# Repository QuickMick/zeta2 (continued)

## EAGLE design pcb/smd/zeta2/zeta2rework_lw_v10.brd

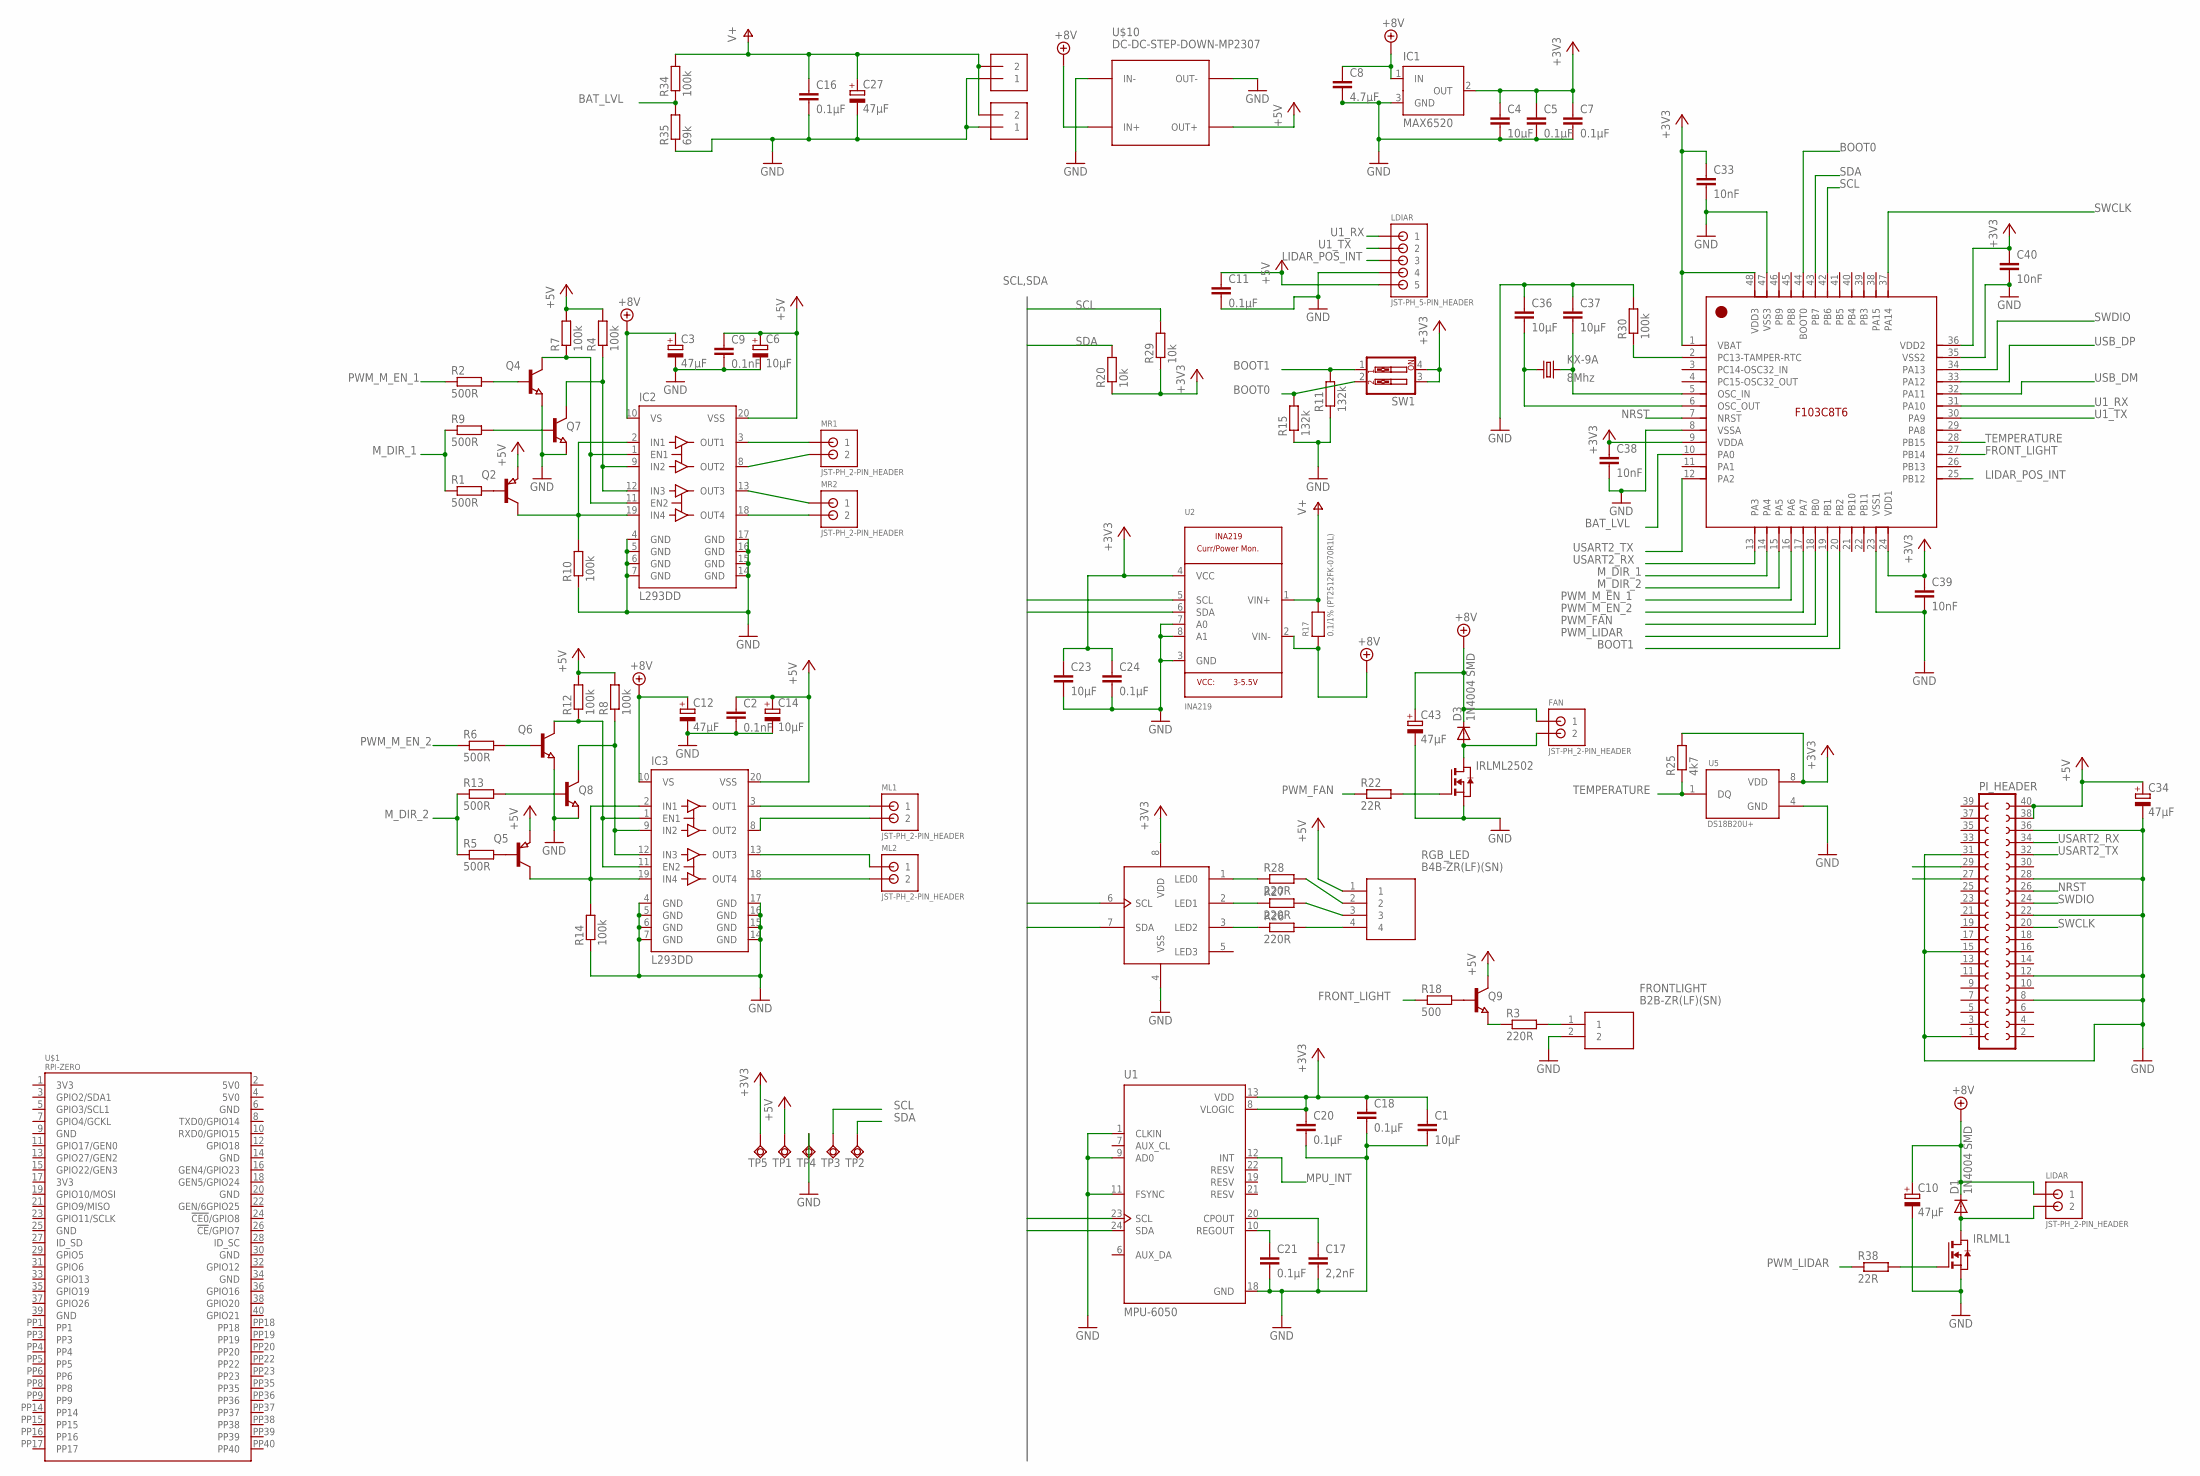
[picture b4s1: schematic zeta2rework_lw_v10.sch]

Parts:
C1, C4, C23, C36, C37: 10µF; C1206
C2, C9: 0.1nF; C1206
C3, C10, C12, C27, C34, C43: 47µF; UD-4X5,8_NICHICON
C5, C7, C11, C16, C18, C20, C21, C24: 0.1µF; C1206
C6, C14: 10µF; UD-4X5,8_NICHICON
C8: 4.7µF; C1206
C17: 2,2nF; C1206
C33, C38, C39, C40: 10nF; C1206
D1, D3: 1N4004 SMD; DO214AC
FAN: JST-PH_2-PIN_HEADER; JST_B2B-PH_HEADER
FRONTLIGHT: B2B-ZR(LF)(SN); SHDR2W50P0X150_1X2_450X350X450
IC1: MAX6520; SOT23
IC2, IC3: L293DD; SO20
IRLML1, IRLML2502: NMOSSOT23; SOT-23
KX-9A: 8Mhz; 5.0X3.2_KX-9A
LDIAR: JST-PH_5-PIN_HEADER; JST_B5B-PH_HEADER
LIDAR: JST-PH_2-PIN_HEADER; JST_B2B-PH_HEADER
ML1, ML2: JST-PH_2-PIN_HEADER; JST_B2B-PH_HEADER
MR1, MR2: JST-PH_2-PIN_HEADER; JST_B2B-PH_HEADER
PCA9533: PCA9533; SOIC8
PI_HEADER: FE20-2
Q2, Q5: PNP-TRANSISTOR_SOT23; SOT23
Q4, Q6, Q7, Q8, Q9: NPN-TRANSISTOR_SOT23; SOT23
R1, R2, R5, R6, R9, R13: 500R; R0603
R3, R26, R27, R28: 220R; R0603
R4, R7, R8, R10, R12, R14, R30, R34: 100k; R0603
R11, R15: 132k; R0603
R17: 0.1/1% (PT2512FK-070R1L); 2512
R18: 500; R1206
R20, R29: 10k; R0603
R22, R38: 22R; R0603
R25: 4k7; R0603
R35: 69k; R0603
RGB_LED: B4B-ZR(LF)(SN); SHDR4W50P0X150_1X4_750X350X450
STM32F103CB: STM32F103CB; LQFP48_7X7MM_0.5MMPP
SUPPLY_IN, SUPPLY_IN1: TERMBLOCK_1X2-3.5MM; 1X2-3.5MM
SW1: SW_DIP-2; EDG-02
TP1, TP2, TP3, TP4, TP5: TPSQTP20R; TP20R
U1: MPU-6050; QFN50P400X400X95-24N
U2: INA219; SOT23-8
U5: DS18B20U+; SOP65P490X95-8N
U$1: RPI-ZERO; RASP_PI_ZERO_BOARD_FULL
U$10: DC-DC-STEP-DOWN-MP2307

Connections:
+3V3: C1.1, C4.1, C5.1, C7.1, C18.1, C20.1, C23.1, C24.1, C33.1, C38.1, C39.1, C40.1, IC1.2 (OUT), PCA9533.8 (VDD), R20.1, R25.2, R29.1, STM32F103CB.1 (VBAT), STM32F103CB.9 (VDDA), STM32F103CB.24 (VDD1), STM32F103CB.36 (VDD2), STM32F103CB.48 (VDD3), SW1.3, SW1.4, TP5.TP, U1.8 (VLOGIC), U1.13 (VDD), U2.4 (VCC), U5.8 (VDD)
+5V: C2.1, C6.+, C9.1, C11.1, C14.+, C34.+, IC2.20 (VSS), IC3.20 (VSS), LDIAR.P5 (5), PI_HEADER.38, PI_HEADER.40, Q2.2 (E), Q5.2 (E), Q9.3 (C), R4.2, R7.2, R8.2, R12.2, RGB_LED.1, TP1.TP, U$10.OUT+
+8V: C3.+, C8.1, C10.+, C12.+, C43.+, D1.C, D3.C, FAN.P1 (1), IC1.1 (IN), IC2.10 (VS), IC3.10 (VS), LIDAR.P1 (1), R17.1, U2.2 (VIN-), U$10.IN+
BAT_LVL: R34.1, R35.2, STM32F103CB.10 (PA0)
BOOT0: R15.2, STM32F103CB.44 (BOOT0), SW1.2
BOOT1: R11.2, STM32F103CB.20 (PB2), SW1.1
BOOT2: PI_HEADER.29
BOOT3: PI_HEADER.27
FRONT_LIGHT: R18.1, STM32F103CB.27 (PB14)
GND: C1.2, C2.2, C3.-, C4.2, C5.2, C6.-, C7.2, C8.2, C9.2, C10.-, C11.2, C12.-, C14.-, C16.2, C17.2, C18.2, C20.2, C21.2, C23.2, C24.2, C27.-, C33.2, C34.-, C36.1, C37.1, C38.2, C39.2, C40.2, C43.-, FRONTLIGHT.2, IC1.3 (GND), IC2.4 (GND), IC2.5 (GND), IC2.6 (GND), IC2.7 (GND), IC2.14 (GND), IC2.15 (GND), IC2.16 (GND), IC2.17 (GND), IC3.4 (GND), IC3.5 (GND), IC3.6 (GND), IC3.7 (GND), IC3.14 (GND), IC3.15 (GND), IC3.16 (GND), IC3.17 (GND), IRLML1.2 (S), IRLML2502.2 (S), LDIAR.P4 (4), PCA9533.4 (VSS), PI_HEADER.1, PI_HEADER.8, PI_HEADER.12, PI_HEADER.15, PI_HEADER.22, PI_HEADER.28, PI_HEADER.31, PI_HEADER.36, Q4.2 (E), Q6.2 (E), Q7.2 (E), Q8.2 (E), R10.1, R11.1, R14.1, R15.1, R30.2, R35.1, STM32F103CB.8 (VSSA), STM32F103CB.23 (VSS1), STM32F103CB.35 (VSS2), STM32F103CB.47 (VSS3), SUPPLY_IN.1, SUPPLY_IN1.1, TP4.TP, U1.1 (CLKIN), U1.9 (AD0), U1.11 (FSYNC), U1.18 (GND), U2.3 (GND), U2.7 (A0), U2.8 (A1), U5.4 (GND), U$10.IN-, U$10.OUT-
LIDAR_POS_INT: LDIAR.P3 (3), STM32F103CB.25 (PB12)
MPU_INT: U1.12 (INT)
M_DIR_1: R1.1, R9.1, STM32F103CB.14 (PA4)
M_DIR_2: R5.1, R13.1, STM32F103CB.15 (PA5)
unnamed: IC2.9 (IN2), IC2.12 (IN3), Q7.3 (C), R4.1
unnamed: IC3.18 (OUT4), ML2.P2 (2)
unnamed: IC3.13 (OUT3), ML2.P1 (1)
unnamed: IC2.18 (OUT4), MR2.P2 (2)
unnamed: IC2.2 (IN1), IC2.19 (IN4), Q2.3 (C), R10.2
unnamed: IC3.9 (IN2), IC3.12 (IN3), Q8.3 (C), R8.1
unnamed: IC3.2 (IN1), IC3.19 (IN4), Q5.3 (C), R14.2
unnamed: IC2.1 (EN1), IC2.11 (EN2), Q4.3 (C), R7.1
unnamed: IC3.1 (EN1), IC3.11 (EN2), Q6.3 (C), R12.1
unnamed: Q2.1 (B), R1.2
unnamed: Q4.1 (B), R2.2
unnamed: Q7.1 (B), R9.2
unnamed: Q5.1 (B), R5.2
unnamed: Q6.1 (B), R6.2
unnamed: Q8.1 (B), R13.2
unnamed: IC2.13 (OUT3), MR2.P1 (1)
unnamed: IC2.8 (OUT2), MR1.P2 (2)
unnamed: IC2.3 (OUT1), MR1.P1 (1)
unnamed: Q9.1 (B), R18.2
unnamed: PCA9533.3 (LED2), R26.1
unnamed: PCA9533.2 (LED1), R27.1
unnamed: PCA9533.1 (LED0), R28.1
unnamed: IC3.8 (OUT2), ML1.P2 (2)
unnamed: IC3.3 (OUT1), ML1.P1 (1)
unnamed: Q9.2 (E), R3.1
unnamed: FRONTLIGHT.1, R3.2
unnamed: R26.2, RGB_LED.4
unnamed: R27.2, RGB_LED.3
unnamed: C17.1, U1.20 (CPOUT)
unnamed: R28.2, RGB_LED.2
unnamed: C21.1, U1.10 (REGOUT)
unnamed: IRLML2502.3 (G), R22.2
unnamed: IRLML1.3 (G), R38.2
unnamed: D1.A, IRLML1.1 (D), LIDAR.P2 (2)
unnamed: C36.2, KX-9A.1, STM32F103CB.6 (OSC_OUT)
unnamed: C37.2, KX-9A.3 (2), STM32F103CB.5 (OSC_IN)
unnamed: R30.1, STM32F103CB.2 (PC13-TAMPER-RTC)
unnamed: D3.A, FAN.P2 (2), IRLML2502.1 (D)
NRST: PI_HEADER.26, STM32F103CB.7 (NRST)
PWM_FAN: R22.1, STM32F103CB.18 (PB0)
PWM_LIDAR: R38.1, STM32F103CB.19 (PB1)
PWM_M_EN_1: R2.1, STM32F103CB.16 (PA6)
PWM_M_EN_2: R6.1, STM32F103CB.17 (PA7)
SCL: PCA9533.6 (SCL), R29.2, STM32F103CB.42 (PB6), TP3.TP, U1.23 (SCL), U2.5 (SCL)
SDA: PCA9533.7 (SDA), R20.2, STM32F103CB.43 (PB7), TP2.TP, U1.24 (SDA), U2.6 (SDA)
SWCLK: PI_HEADER.20, STM32F103CB.37 (PA14)
SWDIO: PI_HEADER.24, STM32F103CB.34 (PA13)
TEMPERATURE: R25.1, STM32F103CB.28 (PB15), U5.1 (DQ)
U1_RX: LDIAR.P1 (1), STM32F103CB.31 (PA10)
U1_TX: LDIAR.P2 (2), STM32F103CB.30 (PA9)
USART2_RX: PI_HEADER.34, STM32F103CB.13 (PA3)
USART2_TX: PI_HEADER.32, STM32F103CB.12 (PA2)
USB_DM: STM32F103CB.32 (PA11)
USB_DP: STM32F103CB.33 (PA12)
V+: C16.1, C27.+, R17.2, R34.2, SUPPLY_IN.2, SUPPLY_IN1.2, U2.1 (VIN+)

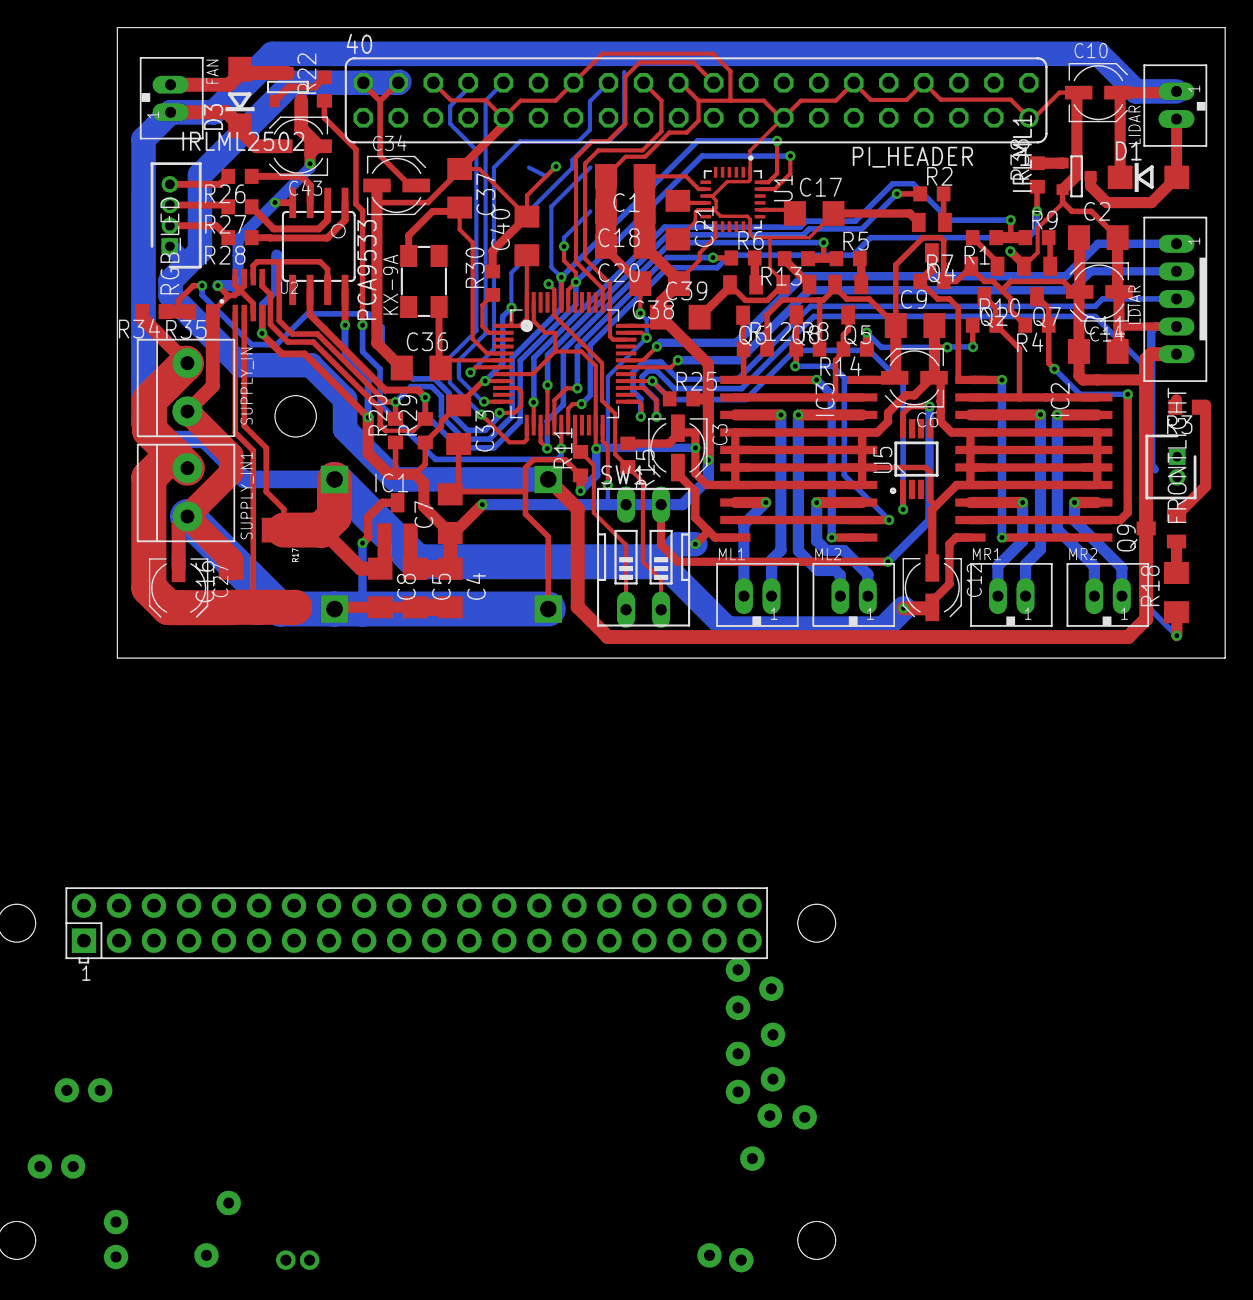
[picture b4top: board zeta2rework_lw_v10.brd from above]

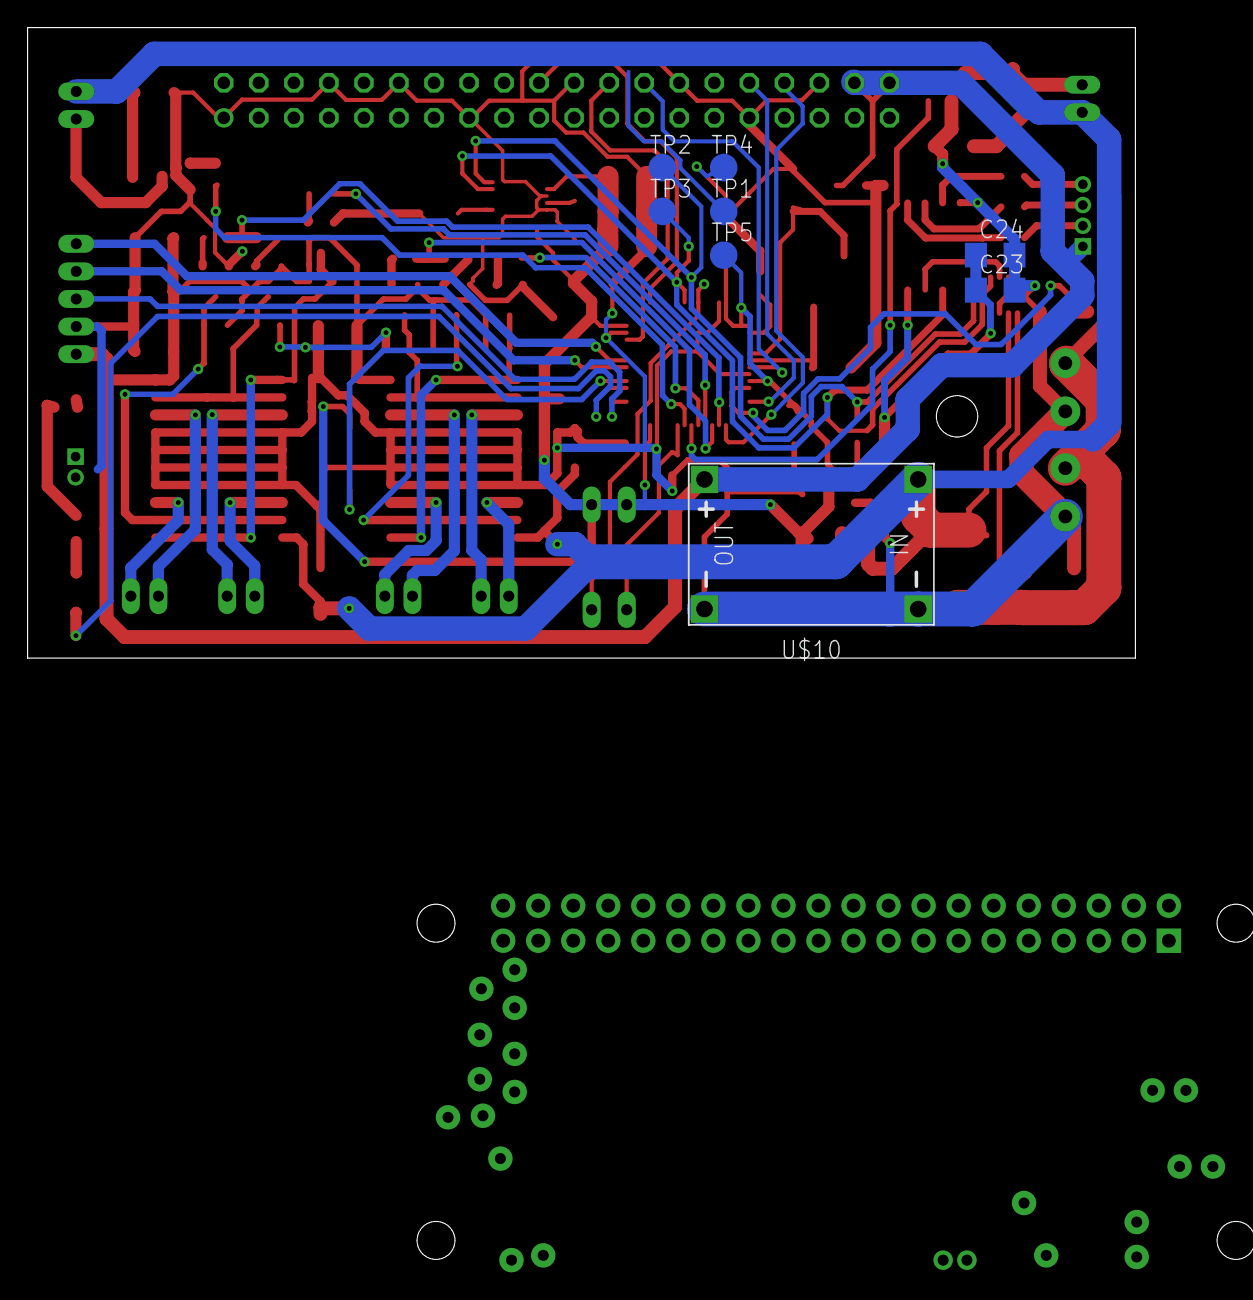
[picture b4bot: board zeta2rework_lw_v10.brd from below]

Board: 2 copper layers, 80.3 x 45.7 mm, 97 parts (8 on the bottom side), 64 nets.
